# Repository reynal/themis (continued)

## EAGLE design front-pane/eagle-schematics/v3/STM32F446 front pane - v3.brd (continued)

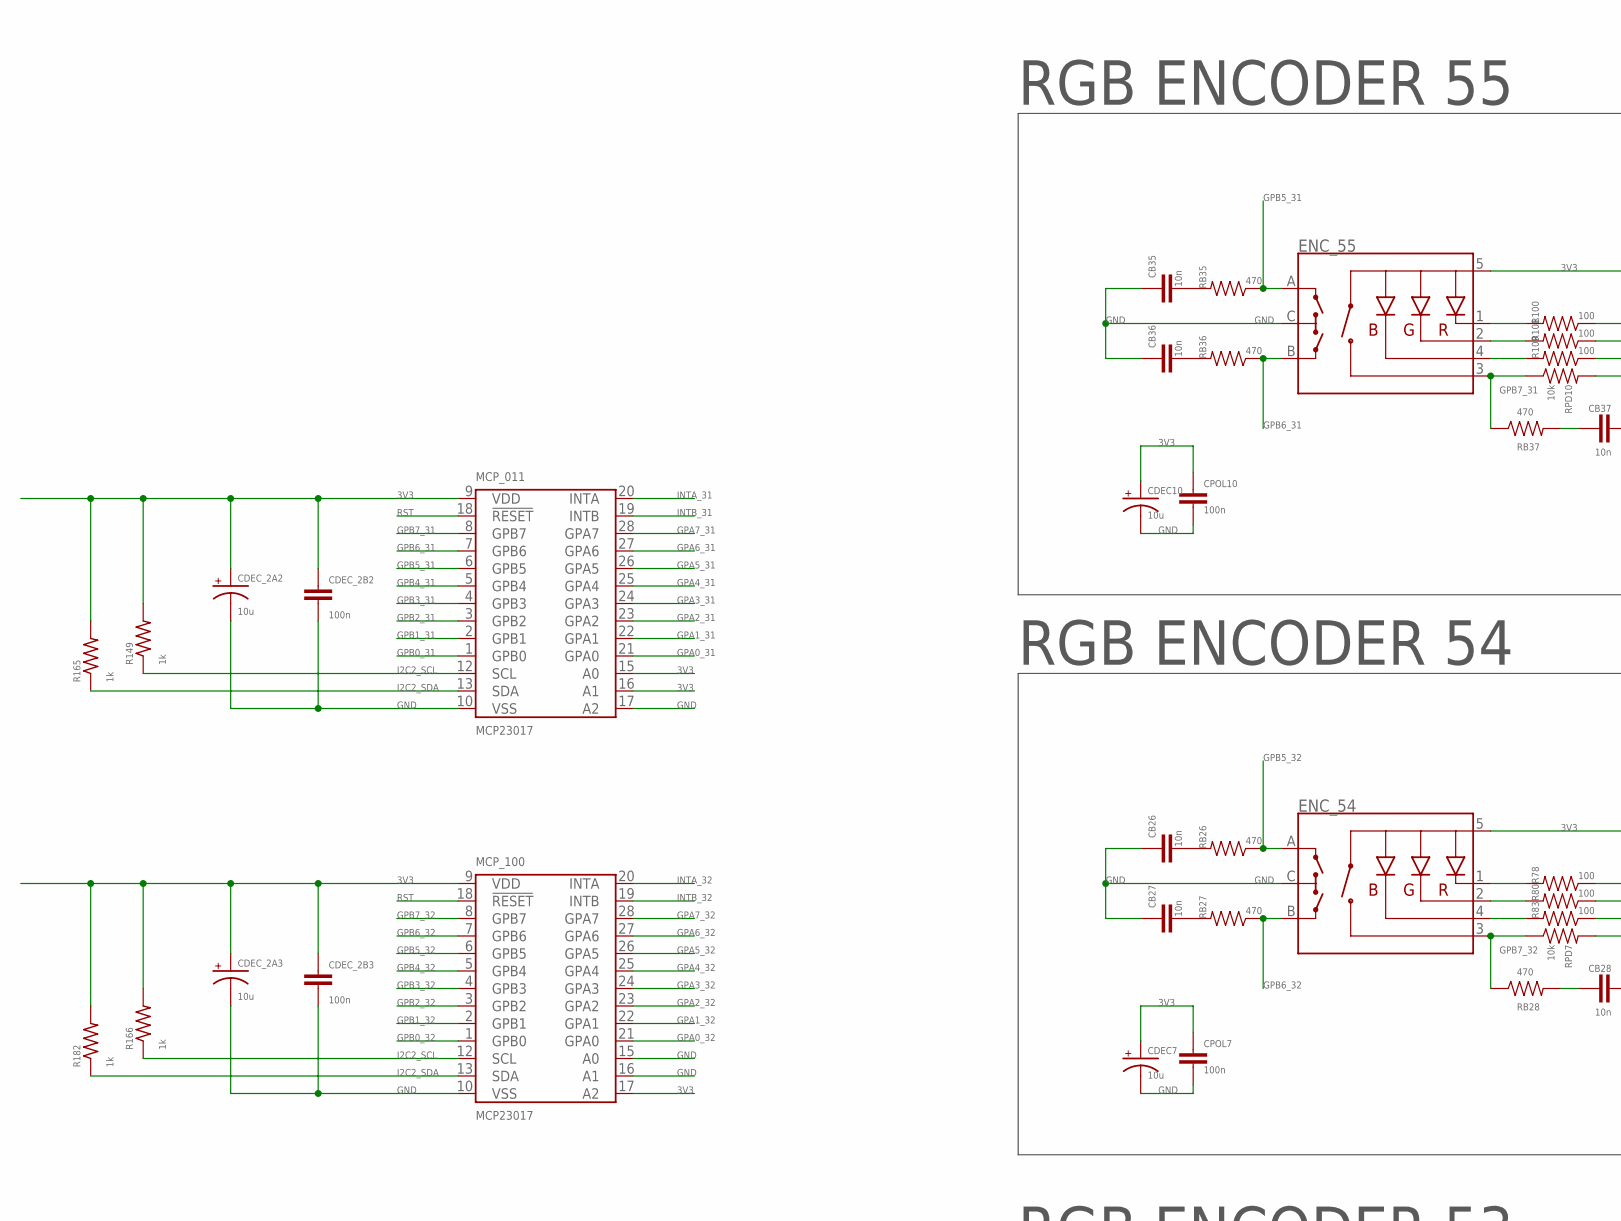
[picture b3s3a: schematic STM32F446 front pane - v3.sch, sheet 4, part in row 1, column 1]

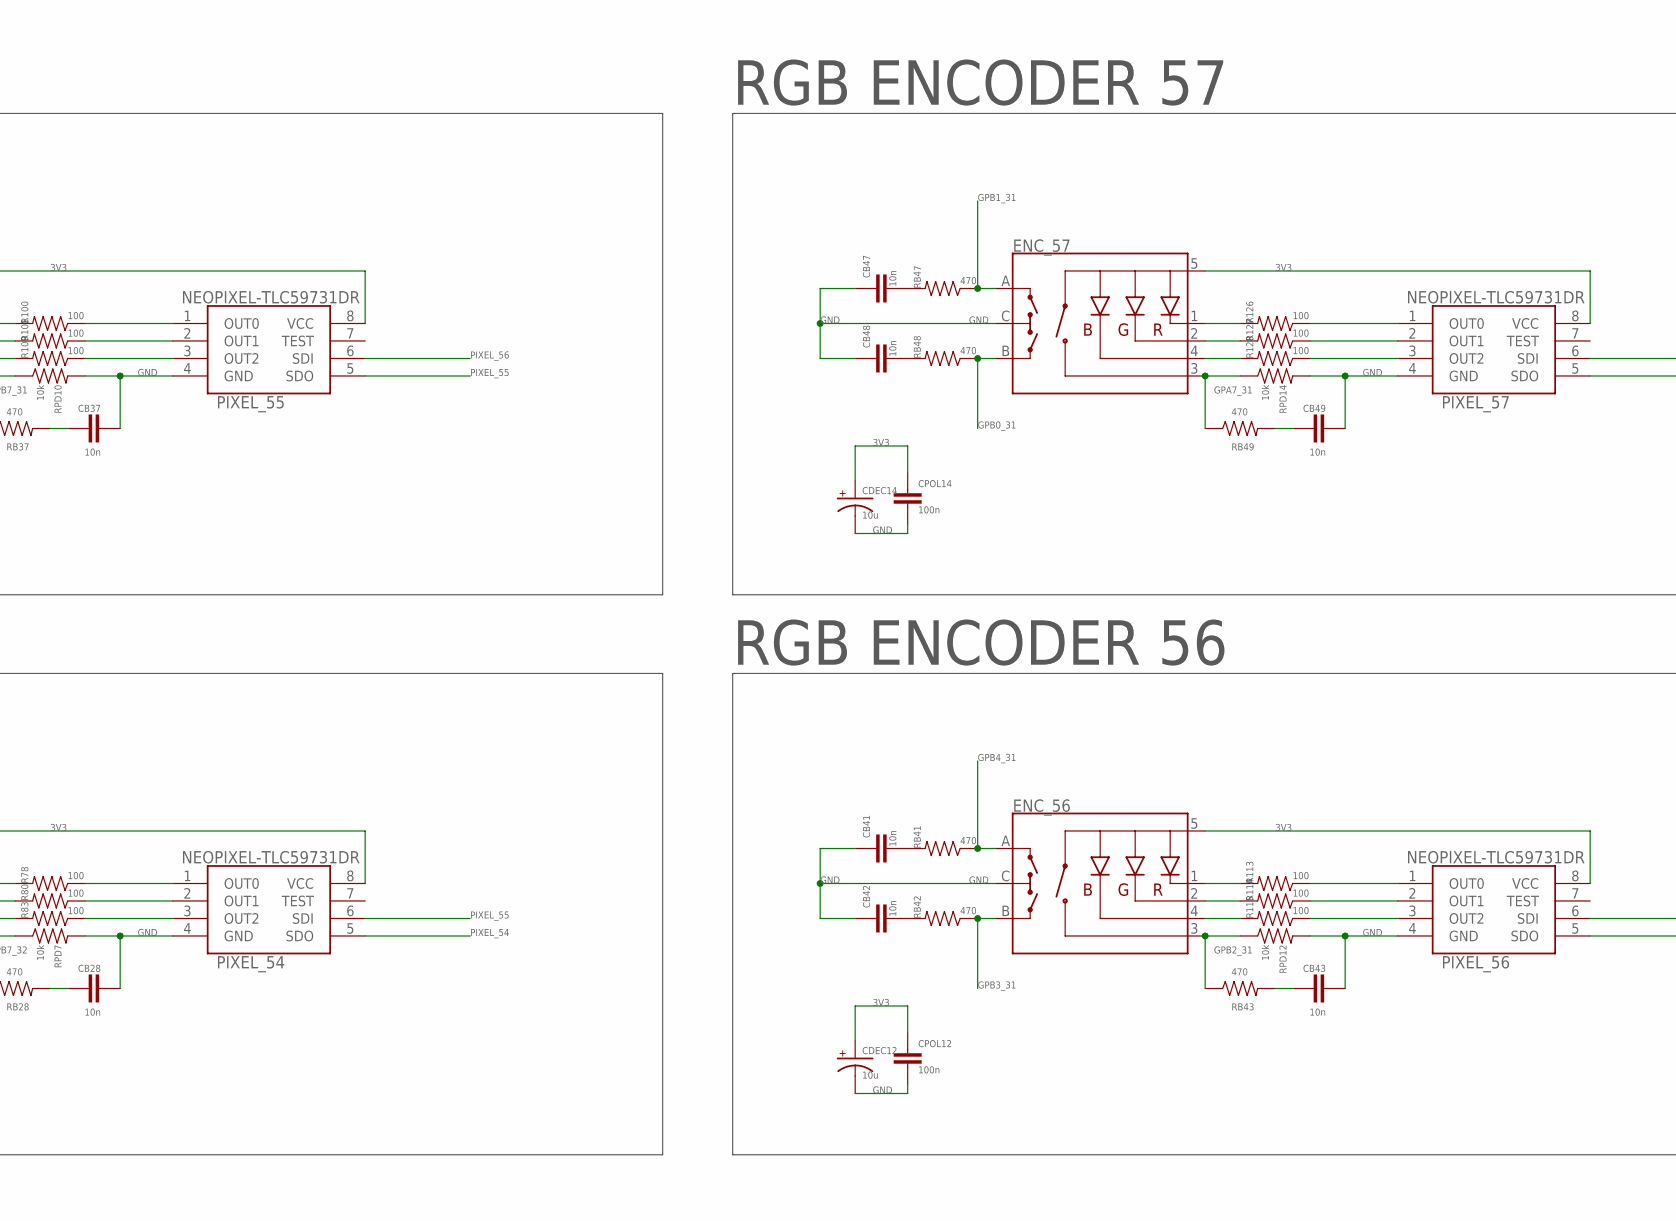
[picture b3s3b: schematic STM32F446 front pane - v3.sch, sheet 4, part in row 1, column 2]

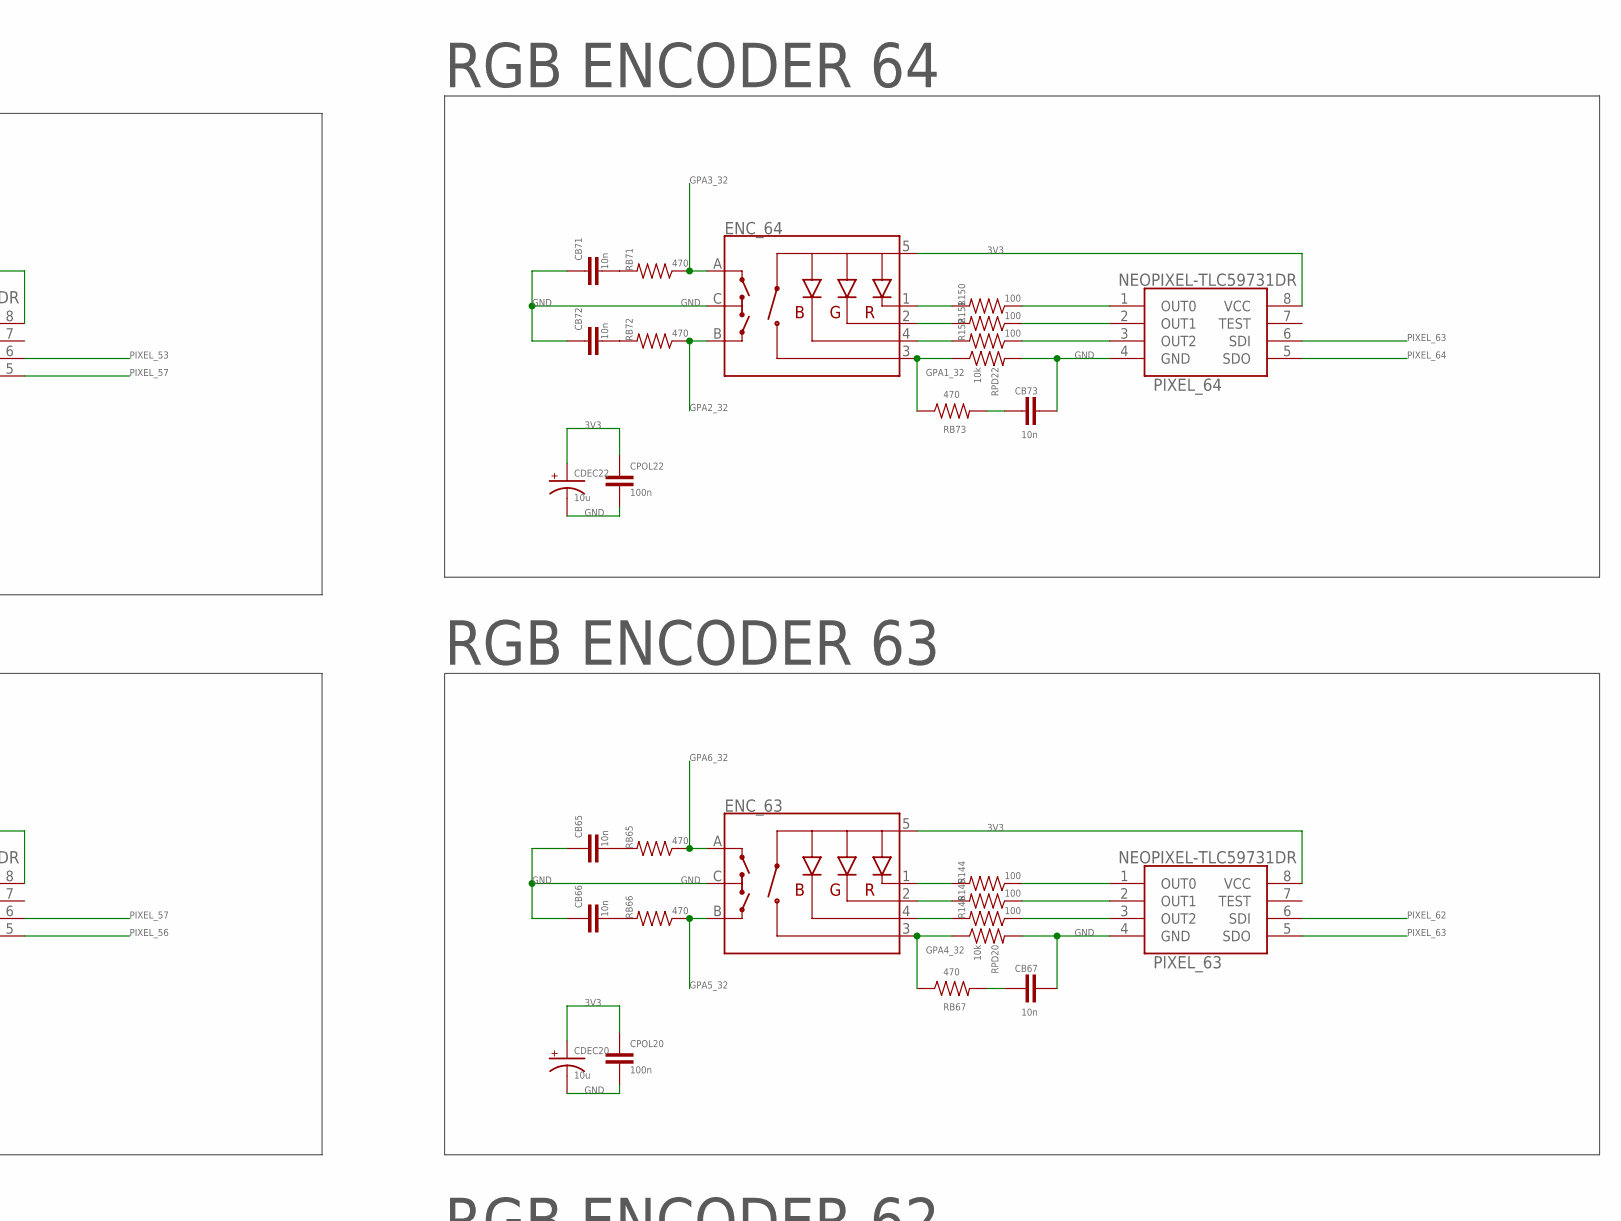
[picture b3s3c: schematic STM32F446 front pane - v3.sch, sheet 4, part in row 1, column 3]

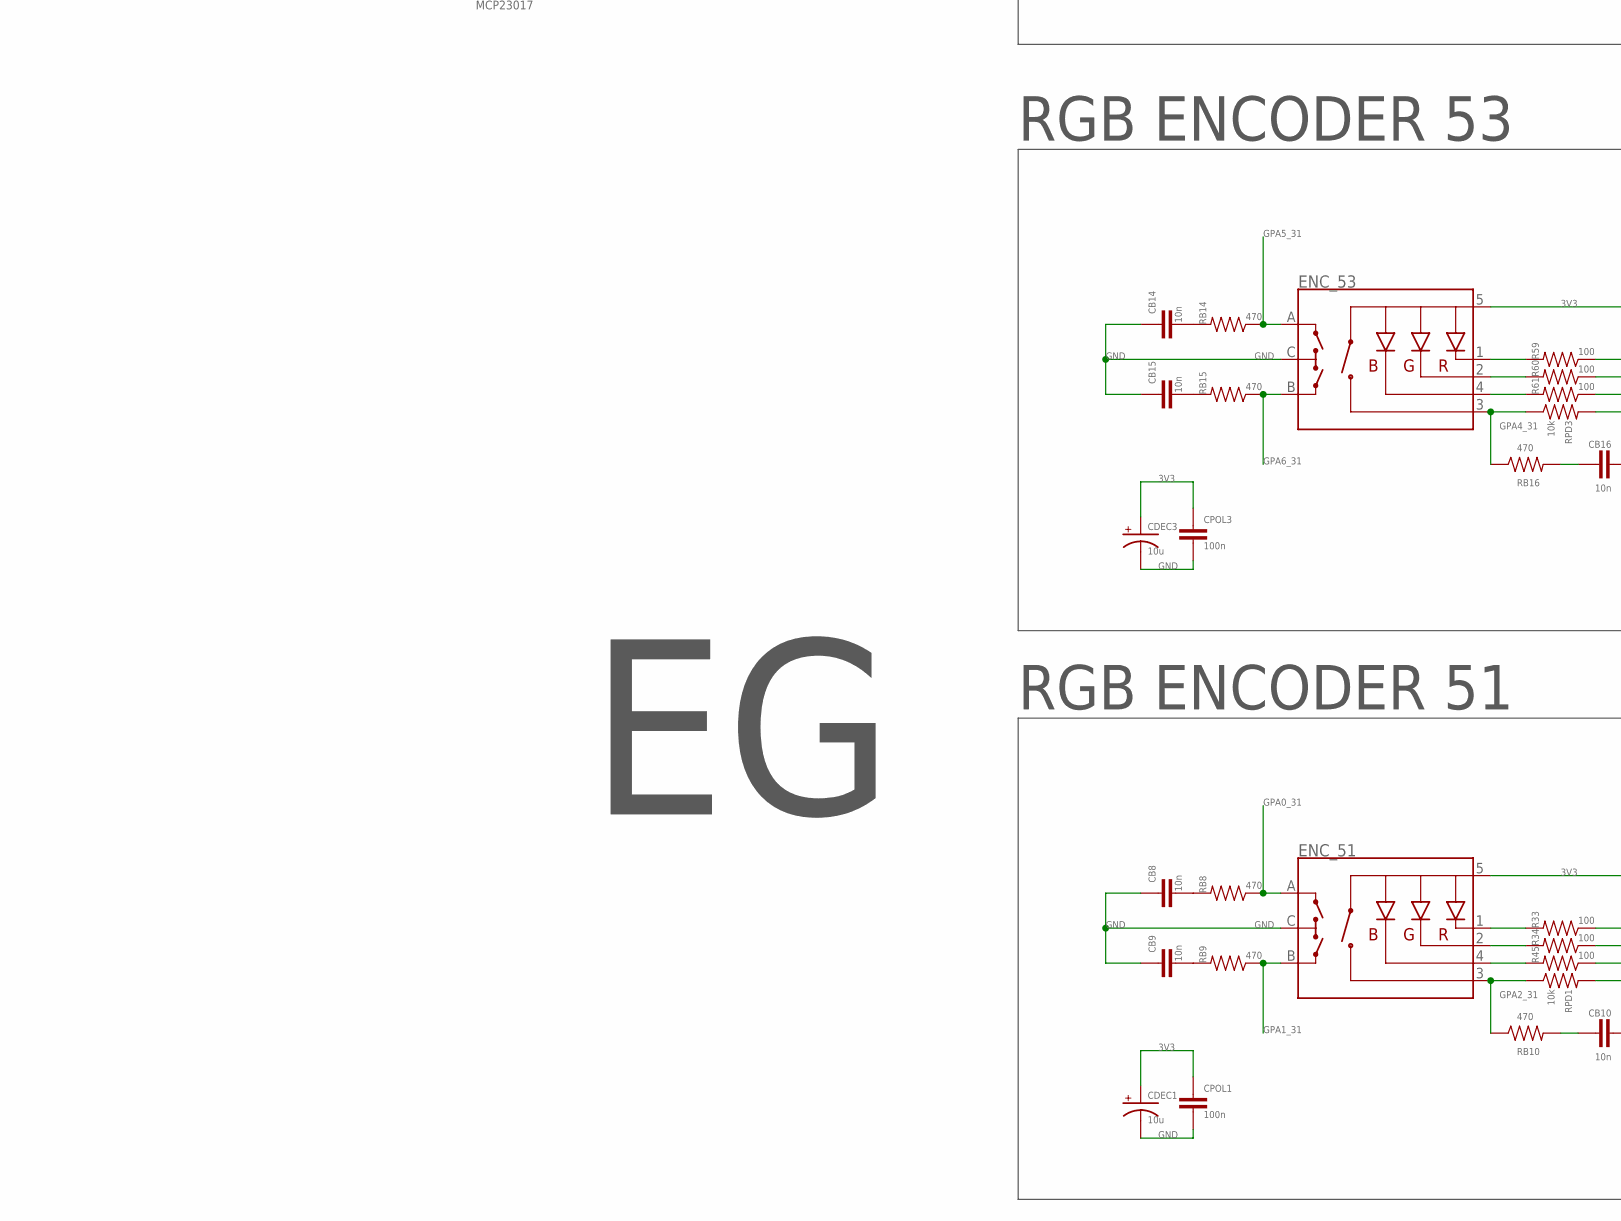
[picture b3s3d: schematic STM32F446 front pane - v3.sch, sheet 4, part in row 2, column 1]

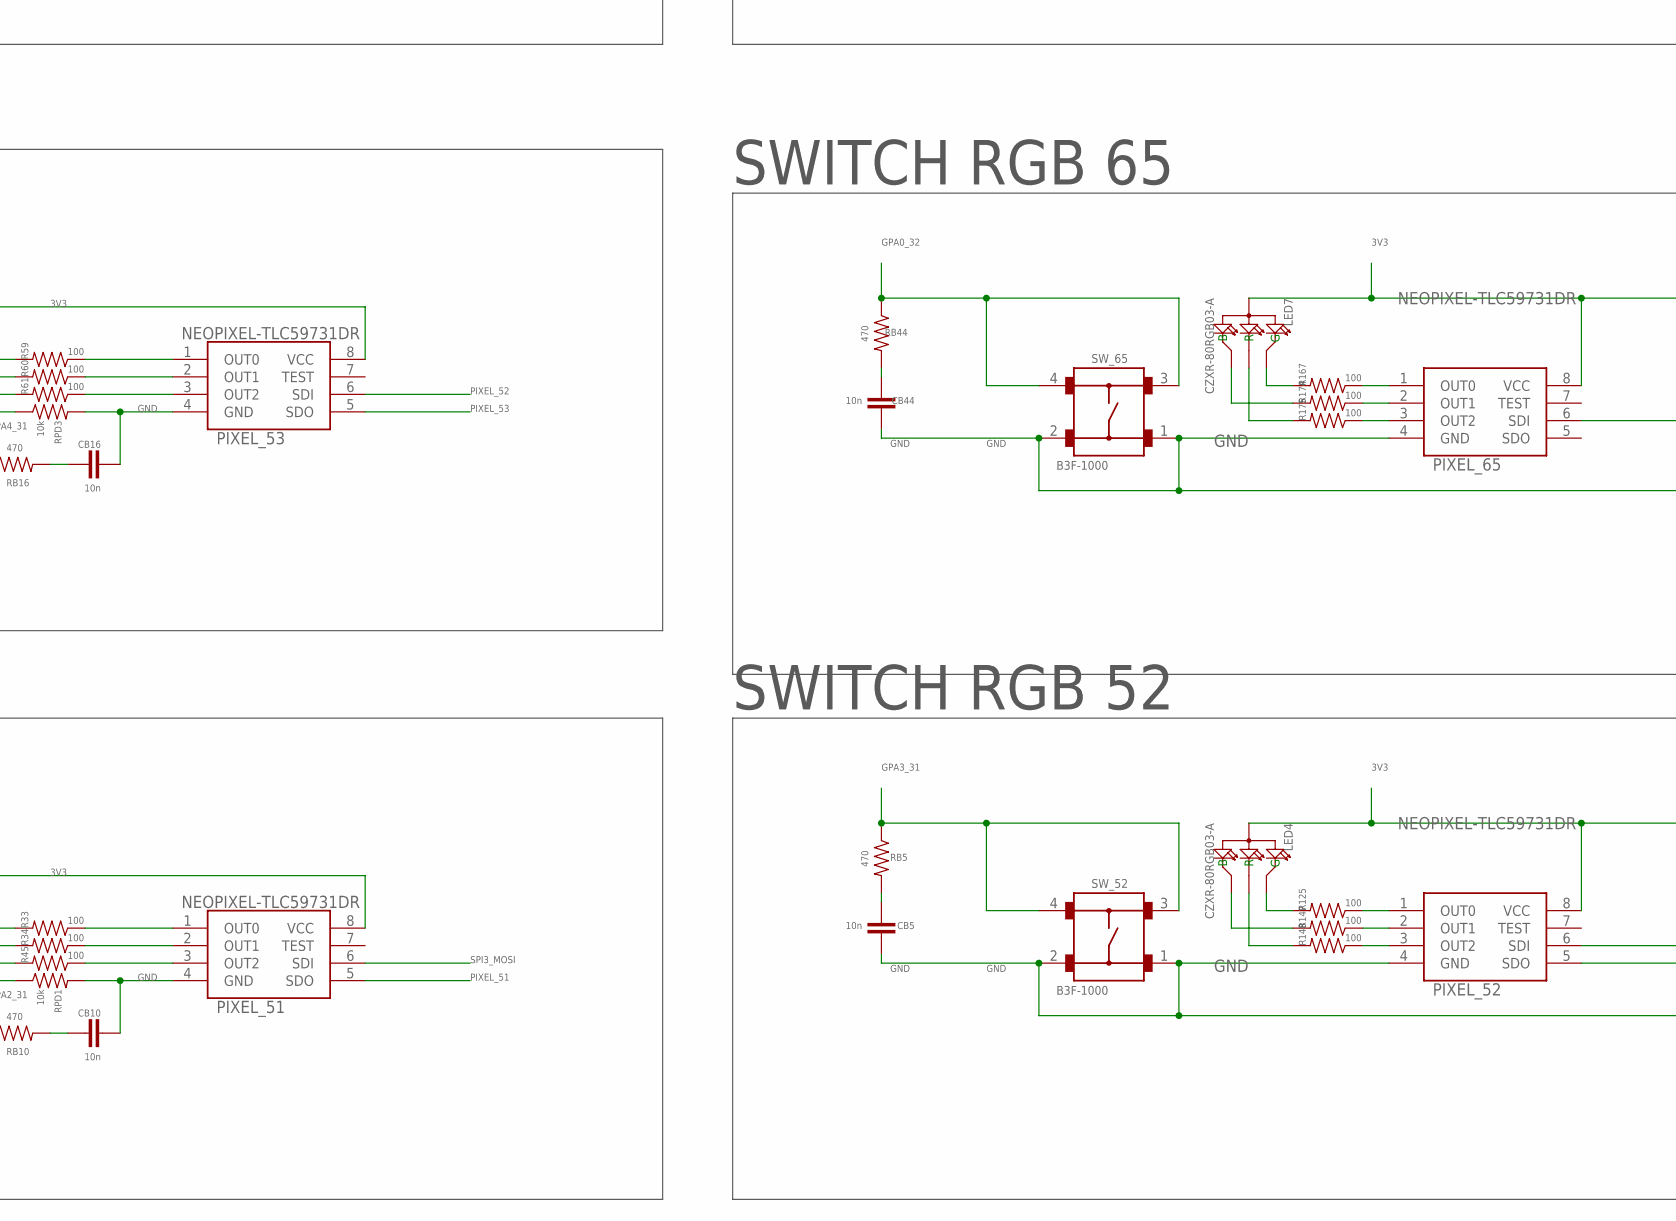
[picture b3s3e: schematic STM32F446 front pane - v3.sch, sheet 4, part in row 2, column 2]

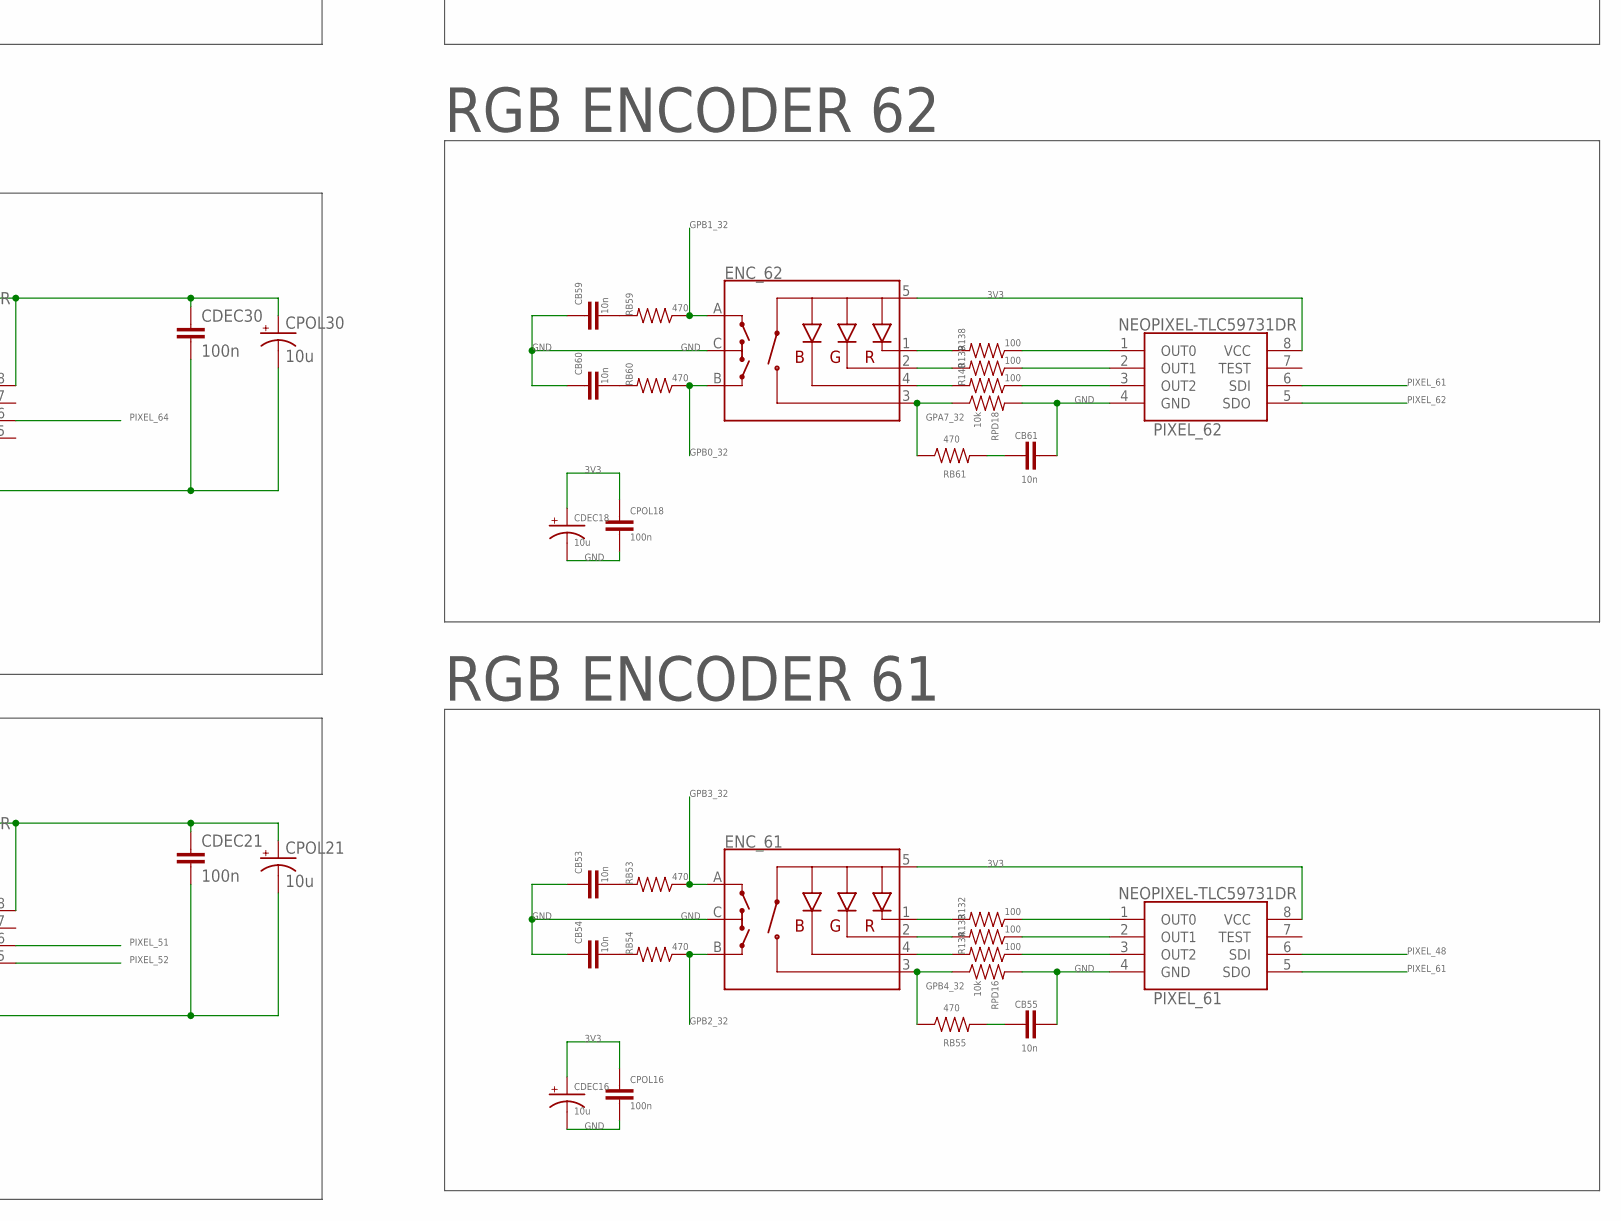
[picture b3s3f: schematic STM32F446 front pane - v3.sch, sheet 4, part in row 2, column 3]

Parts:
CB5, CB8, CB9, CB10, CB14, CB15, CB16, CB26, CB27, CB28, CB35, CB36, CB37, CB41, CB42, CB43, CB44, CB47, CB48, CB49, CB53, CB54, CB55, CB59, CB60, CB61, CB65, CB66, CB67, CB71, CB72, CB73: 10n; 0805-CAP
CDEC1, CDEC3, CDEC7, CDEC10, CDEC12, CDEC14, CDEC16, CDEC18, CDEC20, CDEC22: 10u; CPOL2917
CDEC21, CDEC30: 100n; 0805-CAP
CDEC_2A2, CDEC_2A3: 10u; CPOL2917
CDEC_2B2, CDEC_2B3: 100n; 0805-CAP
CPOL1, CPOL3, CPOL7, CPOL10, CPOL12, CPOL14, CPOL16, CPOL18, CPOL20, CPOL22: 100n; 0805-CAP
CPOL21, CPOL30: 10u; CPOL2917
ENC_51, ENC_53, ENC_54, ENC_55, ENC_56, ENC_57, ENC_61, ENC_62, ENC_63, ENC_64: ENCODER-RGB-SWITCH-NO_NUT; ENCODER_LED_3
LED4, LED7: CZXR-80RGB03-A; LED4-2.0-D8.0MM
MCP_011, MCP_100: MCP23017; SOIC-28
PIXEL_51, PIXEL_52, PIXEL_53, PIXEL_54, PIXEL_55, PIXEL_56, PIXEL_57, PIXEL_61, PIXEL_62, PIXEL_63, PIXEL_64, PIXEL_65: NEOPIXEL-TLC59731DR; SOIC127P600X175-8N
R33, R34, R45, R59, R60, R61, R78, R80, R83, R100, R101, R109, R113, R114, R115, R125, R126, R127, R128, R132, R133, R134, R138, R139, R140, R144, R145, R146, R147, R148, R150, R151, R152, R167, R174, R175: 100; 1206
R149, R165, R166, R182: 1k; R0805
RB5, RB8, RB9, RB10, RB14, RB15, RB16, RB26, RB27, RB28, RB35, RB36, RB37, RB41, RB42, RB43, RB44, RB47, RB48, RB49, RB53, RB54, RB55, RB59, RB60, RB61, RB65, RB66, RB67, RB71, RB72, RB73: 470; 1206
RPD1, RPD3, RPD7, RPD10, RPD12, RPD14, RPD16, RPD18, RPD20, RPD22: 10k; 1206
SW_52, SW_65: B3F-1000

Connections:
3V3: CDEC1.+, CDEC3.+, CDEC7.+, CDEC10.+, CDEC12.+, CDEC14.+, CDEC16.+, CDEC18.+, CDEC20.+, CDEC21.1, CDEC22.+, CDEC30.1, CDEC_2A2.+, CDEC_2A3.+, CDEC_2B2.1, CDEC_2B3.1, CPOL1.1, CPOL3.1, CPOL7.1, CPOL10.1, CPOL12.1, CPOL14.1, CPOL16.1, CPOL18.1, CPOL20.1, CPOL21.+, CPOL22.1, CPOL30.+, ENC_51.5 (+), ENC_53.5 (+), ENC_54.5 (+), ENC_55.5 (+), ENC_56.5 (+), ENC_57.5 (+), ENC_61.5 (+), ENC_62.5 (+), ENC_63.5 (+), ENC_64.5 (+), LED4.2 (+), LED7.2 (+), MCP_011.9 (VDD), MCP_011.15 (A0), MCP_011.16 (A1), MCP_100.9 (VDD), MCP_100.17 (A2), PIXEL_51.8 (VCC), PIXEL_52.8 (VCC), PIXEL_53.8 (VCC), PIXEL_54.8 (VCC), PIXEL_55.8 (VCC), PIXEL_56.8 (VCC), PIXEL_57.8 (VCC), PIXEL_61.8 (VCC), PIXEL_62.8 (VCC), PIXEL_63.8 (VCC), PIXEL_64.8 (VCC), PIXEL_65.8 (VCC), R149.2, R165.2, R166.2, R182.2; also elsewhere on the board
GND: CB5.1, CB8.1, CB9.1, CB10.2, CB14.1, CB15.1, CB16.2, CB26.1, CB27.1, CB28.2, CB35.1, CB36.1, CB37.2, CB41.1, CB42.1, CB43.2, CB44.1, CB47.1, CB48.1, CB49.2, CB53.1, CB54.1, CB55.2, CB59.1, CB60.1, CB61.2, CB65.1, CB66.1, CB67.2, CB71.1, CB72.1, CB73.2, CDEC1.-, CDEC3.-, CDEC7.-, CDEC10.-, CDEC12.-, CDEC14.-, CDEC16.-, CDEC18.-, CDEC20.-, CDEC21.2, CDEC22.-, CDEC30.2, CDEC_2A2.-, CDEC_2A3.-, CDEC_2B2.2, CDEC_2B3.2, CPOL1.2, CPOL3.2, CPOL7.2, CPOL10.2, CPOL12.2, CPOL14.2, CPOL16.2, CPOL18.2, CPOL20.2, CPOL21.-, CPOL22.2, CPOL30.-, ENC_51.C, ENC_53.C, ENC_54.C, ENC_55.C, ENC_56.C, ENC_57.C, ENC_61.C, ENC_62.C, ENC_63.C, ENC_64.C, MCP_011.10 (VSS), MCP_011.17 (A2), MCP_100.10 (VSS), MCP_100.15 (A0), MCP_100.16 (A1), PIXEL_51.4 (GND), PIXEL_52.4 (GND), PIXEL_53.4 (GND), PIXEL_54.4 (GND), PIXEL_55.4 (GND), PIXEL_56.4 (GND), PIXEL_57.4 (GND), PIXEL_61.4 (GND), PIXEL_62.4 (GND), PIXEL_63.4 (GND), PIXEL_64.4 (GND), PIXEL_65.4 (GND), RPD1.2, RPD3.2, RPD7.2, RPD10.2, RPD12.2, RPD14.2, RPD16.2, RPD18.2, RPD20.2, RPD22.2, SW_52.1, SW_52.2, SW_65.1, SW_65.2; also elsewhere on the board
GPA0_31: ENC_51.A, MCP_011.21 (GPA0), RB8.1
GPA0_32: MCP_100.21 (GPA0), RB44.1, SW_65.3, SW_65.4
GPA1_31: ENC_51.B, MCP_011.22 (GPA1), RB9.1
GPA1_32: ENC_64.3 (SW), MCP_100.22 (GPA1), RB73.1, RPD22.1
GPA2_31: ENC_51.3 (SW), MCP_011.23 (GPA2), RB10.1, RPD1.1
GPA2_32: ENC_64.B, MCP_100.23 (GPA2), RB72.1
GPA3_31: MCP_011.24 (GPA3), RB5.1, SW_52.3, SW_52.4
GPA3_32: ENC_64.A, MCP_100.24 (GPA3), RB71.1
GPA4_31: ENC_53.3 (SW), MCP_011.25 (GPA4), RB16.1, RPD3.1
GPA4_32: ENC_63.3 (SW), MCP_100.25 (GPA4), RB67.1, RPD20.1
GPA5_31: ENC_53.A, MCP_011.26 (GPA5), RB14.1
GPA5_32: ENC_63.B, MCP_100.26 (GPA5), RB66.1
GPA6_31: ENC_53.B, MCP_011.27 (GPA6), RB15.1
GPA6_32: ENC_63.A, MCP_100.27 (GPA6), RB65.1
GPA7_31: ENC_57.3 (SW), MCP_011.28 (GPA7), RB49.1, RPD14.1
GPA7_32: ENC_62.3 (SW), MCP_100.28 (GPA7), RB61.1, RPD18.1
GPB0_31: ENC_57.B, MCP_011.1 (GPB0), RB48.1
GPB0_32: ENC_62.B, MCP_100.1 (GPB0), RB60.1
GPB1_31: ENC_57.A, MCP_011.2 (GPB1), RB47.1
GPB1_32: ENC_62.A, MCP_100.2 (GPB1), RB59.1
GPB2_31: ENC_56.3 (SW), MCP_011.3 (GPB2), RB43.1, RPD12.1
GPB2_32: ENC_61.B, MCP_100.3 (GPB2), RB54.1
GPB3_31: ENC_56.B, MCP_011.4 (GPB3), RB42.1
GPB3_32: ENC_61.A, MCP_100.4 (GPB3), RB53.1
GPB4_31: ENC_56.A, MCP_011.5 (GPB4), RB41.1
GPB4_32: ENC_61.3 (SW), MCP_100.5 (GPB4), RB55.1, RPD16.1
GPB5_31: ENC_55.A, MCP_011.6 (GPB5), RB35.1
GPB5_32: ENC_54.A, MCP_100.6 (GPB5), RB26.1
GPB6_31: ENC_55.B, MCP_011.7 (GPB6), RB36.1
GPB6_32: ENC_54.B, MCP_100.7 (GPB6), RB27.1
GPB7_31: ENC_55.3 (SW), MCP_011.8 (GPB7), RB37.1, RPD10.1
GPB7_32: ENC_54.3 (SW), MCP_100.8 (GPB7), RB28.1, RPD7.1
I2C2_SCL: MCP_011.12 (SCL), MCP_100.12 (SCL), R149.1, R166.1; also elsewhere on the board
I2C2_SDA: MCP_011.13 (SDA), MCP_100.13 (SDA), R165.1, R182.1; also elsewhere on the board
INTA_31: MCP_011.20 (INTA); also elsewhere on the board
INTA_32: MCP_100.20 (INTA); also elsewhere on the board
INTB_31: MCP_011.19 (INTB); also elsewhere on the board
INTB_32: MCP_100.19 (INTB); also elsewhere on the board
unnamed: ENC_51.1 (-R), R33.2
unnamed: ENC_51.2 (-G), R34.2
unnamed: ENC_51.4 (-B), R45.2
unnamed: PIXEL_51.1 (OUT0), R33.1
unnamed: PIXEL_51.2 (OUT1), R34.1
unnamed: PIXEL_51.3 (OUT2), R45.1
unnamed: CB8.2, RB8.2
unnamed: CB9.2, RB9.2
unnamed: CB10.1, RB10.2
unnamed: ENC_53.1 (-R), R59.2
unnamed: ENC_53.2 (-G), R60.2
unnamed: ENC_53.4 (-B), R61.2
unnamed: PIXEL_53.1 (OUT0), R59.1
unnamed: PIXEL_53.2 (OUT1), R60.1
unnamed: PIXEL_53.3 (OUT2), R61.1
unnamed: CB14.2, RB14.2
unnamed: CB15.2, RB15.2
unnamed: CB16.1, RB16.2
unnamed: ENC_54.1 (-R), R78.2
unnamed: ENC_54.2 (-G), R80.2
unnamed: ENC_54.4 (-B), R83.2
unnamed: PIXEL_54.1 (OUT0), R78.1
unnamed: PIXEL_54.2 (OUT1), R80.1
unnamed: PIXEL_54.3 (OUT2), R83.1
unnamed: CB26.2, RB26.2
unnamed: CB27.2, RB27.2
unnamed: CB28.1, RB28.2
unnamed: ENC_55.1 (-R), R100.2
unnamed: ENC_55.2 (-G), R101.2
unnamed: ENC_55.4 (-B), R109.2
unnamed: PIXEL_55.1 (OUT0), R100.1
unnamed: PIXEL_55.2 (OUT1), R101.1
unnamed: PIXEL_55.3 (OUT2), R109.1
unnamed: CB35.2, RB35.2
unnamed: CB36.2, RB36.2
unnamed: CB37.1, RB37.2
unnamed: ENC_56.1 (-R), R113.2
unnamed: ENC_56.2 (-G), R114.2
unnamed: ENC_56.4 (-B), R115.2
unnamed: PIXEL_56.1 (OUT0), R113.1
unnamed: PIXEL_56.2 (OUT1), R114.1
unnamed: PIXEL_56.3 (OUT2), R115.1
unnamed: CB41.2, RB41.2
unnamed: CB42.2, RB42.2
unnamed: CB43.1, RB43.2
unnamed: PIXEL_52.1 (OUT0), R125.1
unnamed: PIXEL_52.2 (OUT1), R147.1
unnamed: PIXEL_52.3 (OUT2), R148.1
unnamed: CB5.2, RB5.2
unnamed: ENC_57.1 (-R), R126.2
unnamed: ENC_57.2 (-G), R127.2
unnamed: ENC_57.4 (-B), R128.2
unnamed: PIXEL_57.1 (OUT0), R126.1
unnamed: PIXEL_57.2 (OUT1), R127.1
unnamed: PIXEL_57.3 (OUT2), R128.1
unnamed: CB47.2, RB47.2
unnamed: CB48.2, RB48.2
unnamed: CB49.1, RB49.2
unnamed: ENC_61.1 (-R), R132.2
unnamed: ENC_61.2 (-G), R133.2
unnamed: ENC_61.4 (-B), R134.2
unnamed: PIXEL_61.1 (OUT0), R132.1
unnamed: PIXEL_61.2 (OUT1), R133.1
unnamed: PIXEL_61.3 (OUT2), R134.1
unnamed: CB53.2, RB53.2
unnamed: CB54.2, RB54.2
unnamed: CB55.1, RB55.2
unnamed: ENC_62.1 (-R), R138.2
unnamed: ENC_62.2 (-G), R139.2
unnamed: ENC_62.4 (-B), R140.2
unnamed: PIXEL_62.1 (OUT0), R138.1
unnamed: PIXEL_62.2 (OUT1), R139.1
unnamed: PIXEL_62.3 (OUT2), R140.1
unnamed: CB59.2, RB59.2
unnamed: CB60.2, RB60.2
unnamed: CB61.1, RB61.2
unnamed: ENC_63.1 (-R), R144.2
unnamed: ENC_63.2 (-G), R145.2
unnamed: ENC_63.4 (-B), R146.2
unnamed: PIXEL_63.1 (OUT0), R144.1
unnamed: PIXEL_63.2 (OUT1), R145.1
unnamed: PIXEL_63.3 (OUT2), R146.1
unnamed: CB65.2, RB65.2
unnamed: CB66.2, RB66.2
unnamed: CB67.1, RB67.2
unnamed: LED4.1 (R), R148.2
unnamed: LED4.4 (B), R147.2
unnamed: LED4.3 (G), R125.2
unnamed: ENC_64.1 (-R), R150.2
unnamed: ENC_64.2 (-G), R151.2
unnamed: ENC_64.4 (-B), R152.2
unnamed: PIXEL_64.1 (OUT0), R150.1
unnamed: PIXEL_64.2 (OUT1), R151.1
unnamed: PIXEL_64.3 (OUT2), R152.1
unnamed: CB71.2, RB71.2
unnamed: CB72.2, RB72.2
unnamed: CB73.1, RB73.2
unnamed: PIXEL_65.1 (OUT0), R167.1
unnamed: PIXEL_65.2 (OUT1), R174.1
unnamed: PIXEL_65.3 (OUT2), R175.1
unnamed: CB44.2, RB44.2
unnamed: LED7.1 (R), R175.2
unnamed: LED7.4 (B), R174.2
unnamed: LED7.3 (G), R167.2
PIXEL_48: PIXEL_61.6 (SDI); also elsewhere on the board
PIXEL_51: PIXEL_51.5 (SDO), PIXEL_52.6 (SDI)
PIXEL_52: PIXEL_52.5 (SDO), PIXEL_53.6 (SDI)
PIXEL_53: PIXEL_53.5 (SDO), PIXEL_57.6 (SDI)
PIXEL_54: PIXEL_54.5 (SDO); also elsewhere on the board
PIXEL_55: PIXEL_54.6 (SDI), PIXEL_55.5 (SDO)
PIXEL_56: PIXEL_55.6 (SDI), PIXEL_56.5 (SDO)
PIXEL_57: PIXEL_56.6 (SDI), PIXEL_57.5 (SDO)
PIXEL_61: PIXEL_61.5 (SDO), PIXEL_62.6 (SDI)
PIXEL_62: PIXEL_62.5 (SDO), PIXEL_63.6 (SDI)
PIXEL_63: PIXEL_63.5 (SDO), PIXEL_64.6 (SDI)
PIXEL_64: PIXEL_64.5 (SDO), PIXEL_65.6 (SDI)
RST: MCP_011.18 (!RESET), MCP_100.18 (!RESET); also elsewhere on the board
SPI3_MOSI: PIXEL_51.6 (SDI); also elsewhere on the board

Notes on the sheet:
RGB ENCODER 51
RGB ENCODER 53
RGB ENCODER 54
RGB ENCODER 55
RGB ENCODER 56
RGB ENCODER 57
RGB ENCODER 61
RGB ENCODER 62
RGB ENCODER 63
RGB ENCODER 64
SWITCH RGB 52
SWITCH RGB 65
